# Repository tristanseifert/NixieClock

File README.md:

# Nixie Clock
A Nixie tube clock based on the Russian [IN-12A](http://www.tube-tester.com/sites/nixie/data/in-12a.htm) tubes. The clock is designed to be modular: one or more tube boards (which contain value latches, high voltage drivers, tube mounts, and current limiting resistors) can be connected to the control board (which contains a full 68008-based minicomputer!)

There is also provision for an USB FIFO (FT245R) for communication with a PC, a 32K NVRAM+RTC (DS1244) for timekeeping and configuration, a 100Hz periodic interrupt, and a connection to a Noritake CU24043-Y100 (or any other display with the same pinout) VFD.

The board is powered off of a regulated 12V supply, from which 5V and ~180V (for the anodes) is generated.

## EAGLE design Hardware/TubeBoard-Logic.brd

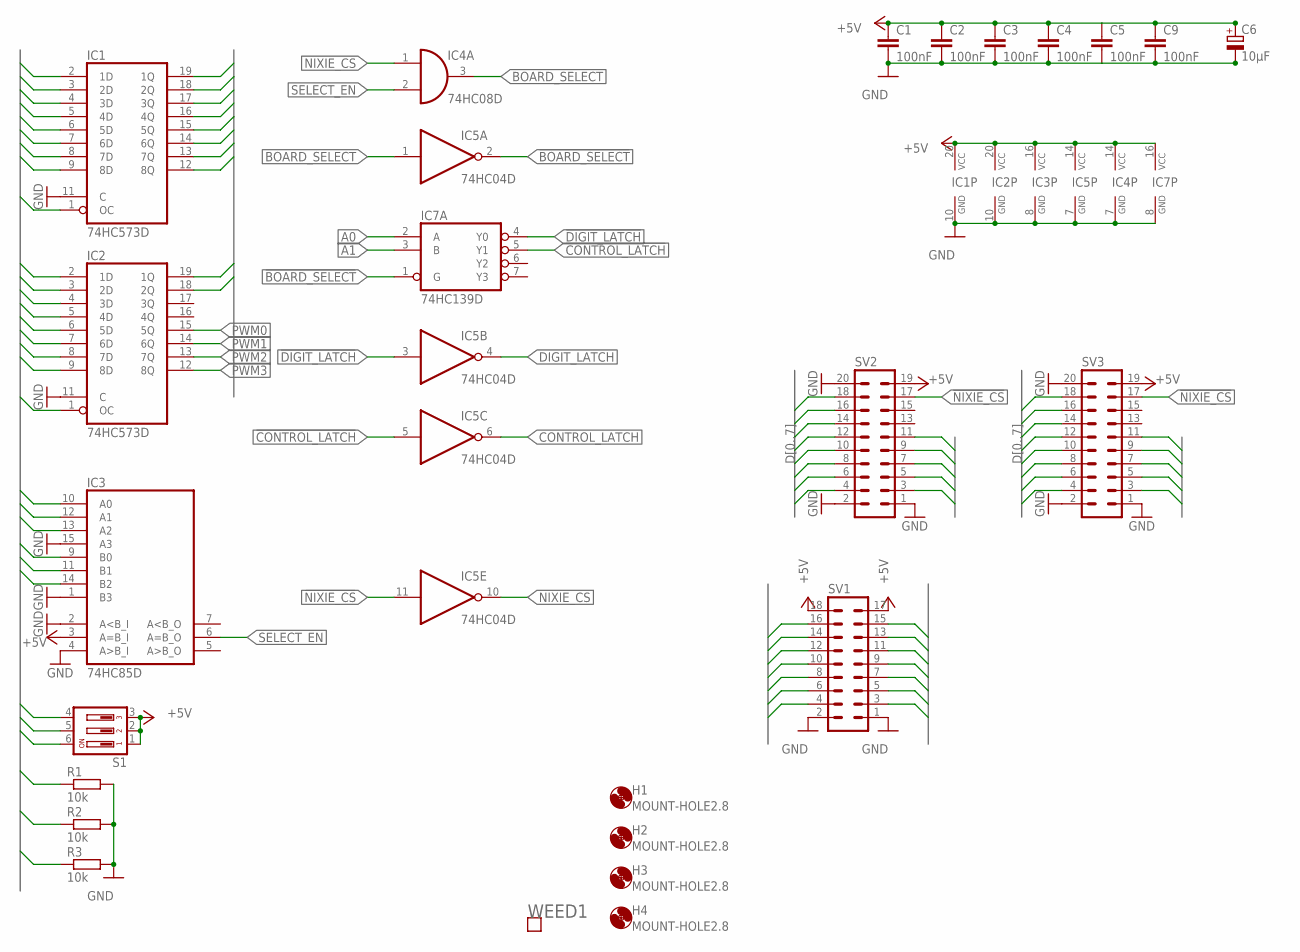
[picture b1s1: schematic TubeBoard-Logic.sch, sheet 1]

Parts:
C1, C2, C3, C4, C5, C9: 100nF; C1206
C6: 10µF; SMC_B; MOUSER 581-TAJB106K020RNJV
H1, H2, H3, H4: MOUNT-HOLE2.8; 2,8
IC1, IC2: 74HC573D; SO20W
IC3: 74HC85D; SO16; MOUSER 771-74HC85D-T
IC4: 74HC08D; SO14
IC5: 74HC04D; SO14
IC7: 74HC139D; SO16; MOUSER 771-HC139D652
R1, R2, R3: 10k; R2012; MOUSER 652-CR0805FX-1002ELF
S1: SD4-03; MOUSER 611-BDB03
SV1: MA09-2
SV2, SV3: MA10-2
WEED1: WEED; DOINK

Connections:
!BOARD_SELECT: IC5.2 (O), IC7.1 (G)
!CONTROL_LATCH: IC5.5 (I), IC7.5 (Y1)
!DIGIT_LATCH: IC5.3 (I), IC7.4 (Y0)
!NIXIE_CS: IC5.11 (I), SV2.17, SV3.17
+5V: C1.1, C2.1, C3.1, C4.1, C5.1, C6.+, C9.1, IC1.20 (VCC), IC2.20 (VCC), IC3.3 (A=B_I), IC3.16 (VCC), IC4.14 (VCC), IC5.14 (VCC), IC7.16 (VCC), S1.1, S1.2, S1.3, SV1.17, SV1.18, SV2.19, SV3.19
A0: IC7.2 (A), SV2.3, SV3.3
A1: IC7.3 (B), SV2.5, SV3.5
A2: IC3.10 (A0), SV2.7, SV3.7
A3: IC3.12 (A1), SV2.9, SV3.9
A4: IC3.13 (A2), SV2.11, SV3.11
BOARD_SELECT: IC4.3 (O), IC5.1 (I)
COLON_B: IC2.19 (1Q), SV1.8
COLON_T: IC2.18 (2Q), SV1.6
CONTROL_LATCH: IC2.1 (OC), IC5.6 (O)
D0: IC1.2 (1D), IC2.2 (1D), SV2.8, SV3.8
D1: IC1.3 (2D), IC2.3 (2D), SV2.6, SV3.6
D2: IC1.4 (3D), IC2.4 (3D), SV2.4, SV3.4
D3: IC1.5 (4D), IC2.5 (4D), SV2.10, SV3.10
D4: IC1.6 (5D), IC2.6 (5D), SV2.12, SV3.12
D5: IC1.7 (6D), IC2.7 (6D), SV2.14, SV3.14
D6: IC1.8 (7D), IC2.8 (7D), SV2.16, SV3.16
D7: IC1.9 (8D), IC2.9 (8D), SV2.18, SV3.18
DIGIT_LATCH: IC1.1 (OC), IC5.4 (O)
GND: C1.2, C2.2, C3.2, C4.2, C5.2, C6.-, C9.2, IC1.10 (GND), IC1.11 (C), IC2.10 (GND), IC2.11 (C), IC3.1 (B3), IC3.2 (A<B_I), IC3.4 (A>B_I), IC3.8 (GND), IC3.15 (A3), IC4.7 (GND), IC5.7 (GND), IC7.8 (GND), R1.2, R2.2, R3.2, SV1.1, SV1.2, SV2.1, SV2.2, SV2.20, SV3.1, SV3.2, SV3.20; also elsewhere on the board
ID0: IC3.9 (B0), R3.1, S1.6
ID1: IC3.11 (B1), R2.1, S1.5
ID2: IC3.14 (B2), R1.1, S1.4
LDIGIT0: IC1.19 (1Q), SV1.16
LDIGIT1: IC1.18 (2Q), SV1.14
LDIGIT2: IC1.17 (3Q), SV1.12
LDIGIT3: IC1.16 (4Q), SV1.10
NIXIE_CS: IC4.1 (I0), IC5.10 (O)
PWM0: IC2.15 (5Q), SV1.7
PWM1: IC2.14 (6Q), SV1.5
PWM2: IC2.13 (7Q), SV1.3
PWM3: IC2.12 (8Q), SV1.4
RDIGIT0: IC1.15 (5Q), SV1.15
RDIGIT1: IC1.14 (6Q), SV1.13
RDIGIT2: IC1.13 (7Q), SV1.11
RDIGIT3: IC1.12 (8Q), SV1.9
SELECT_EN: IC3.6 (A=B_O), IC4.2 (I1)

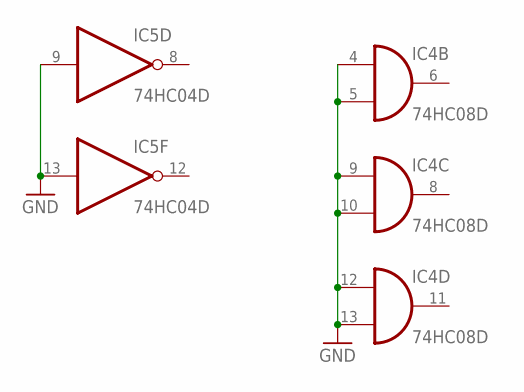
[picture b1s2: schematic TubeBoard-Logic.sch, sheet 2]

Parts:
IC4: 74HC08D; SO14
IC5: 74HC04D; SO14

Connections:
GND: IC4.4 (I0), IC4.5 (I1), IC4.9 (I0), IC4.10 (I1), IC4.12 (I0), IC4.13 (I1), IC5.9 (I), IC5.13 (I); also elsewhere on the board

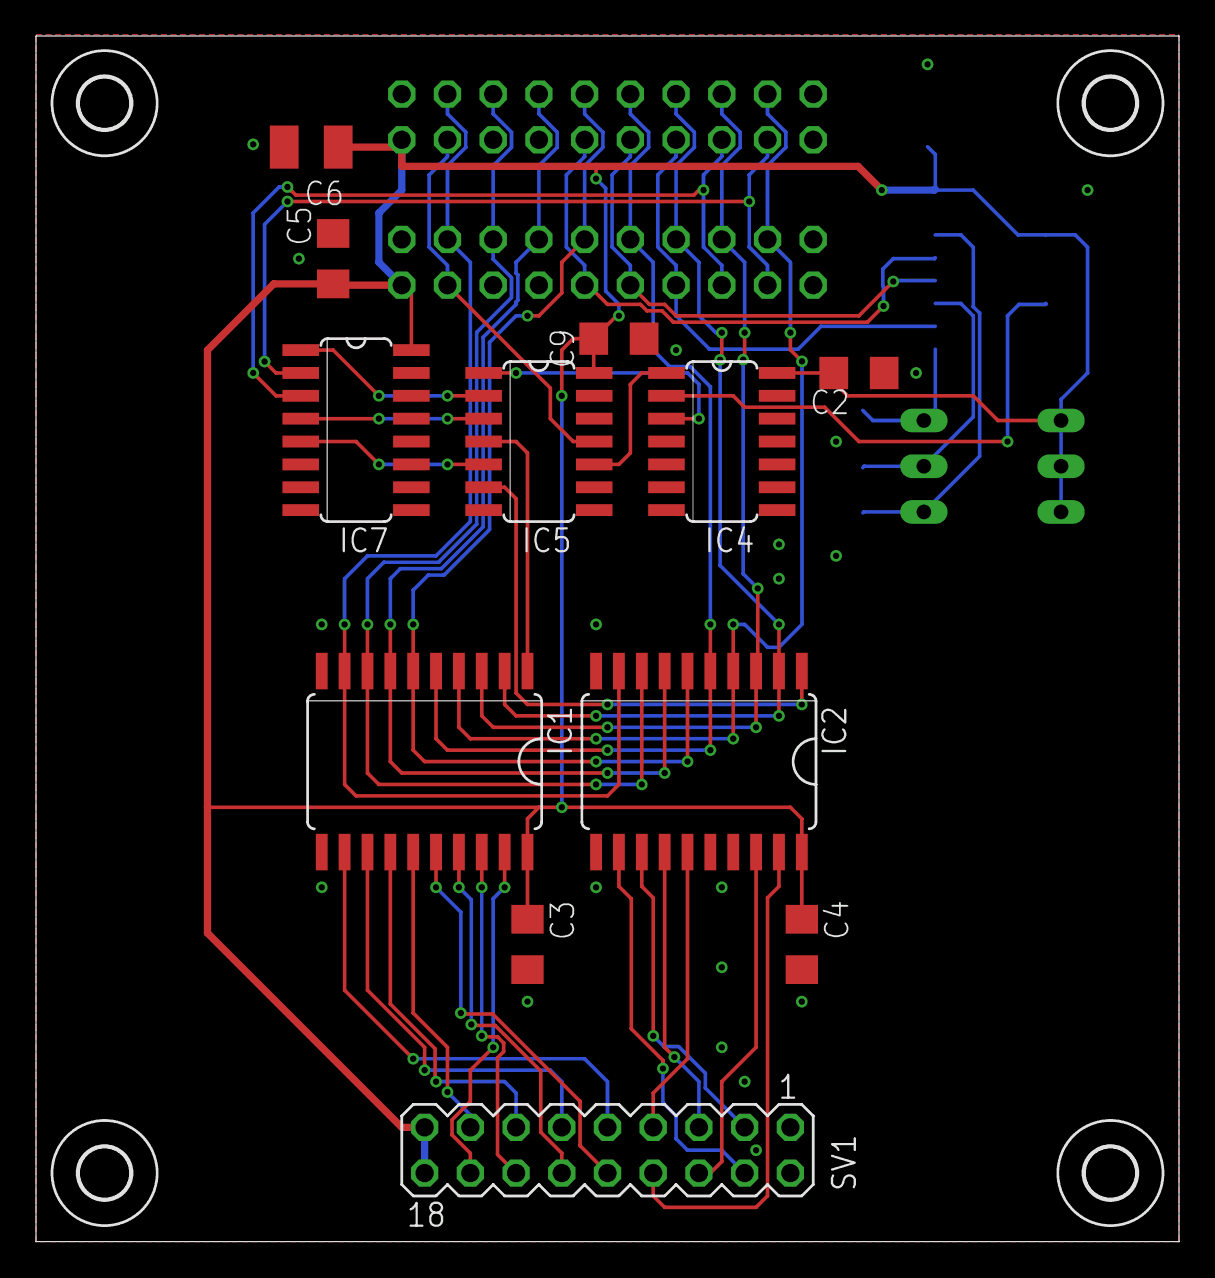
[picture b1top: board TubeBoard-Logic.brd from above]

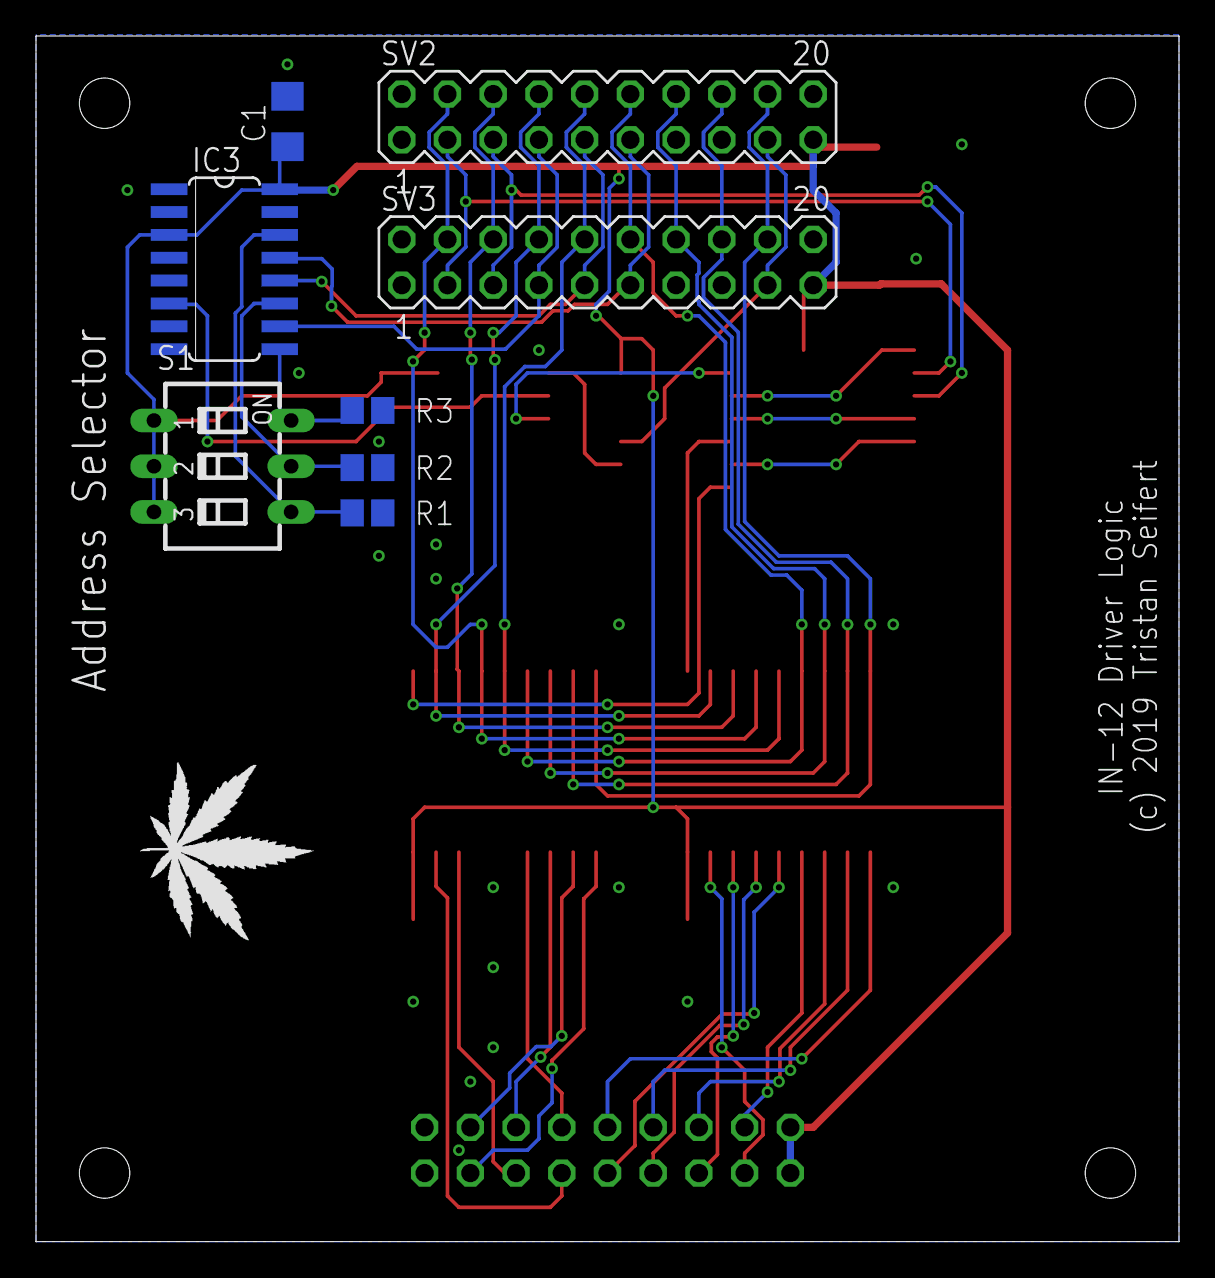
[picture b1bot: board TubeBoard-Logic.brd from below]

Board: 2 copper layers, 63.5 x 67.0 mm, 25 parts (9 on the bottom side), 41 nets.

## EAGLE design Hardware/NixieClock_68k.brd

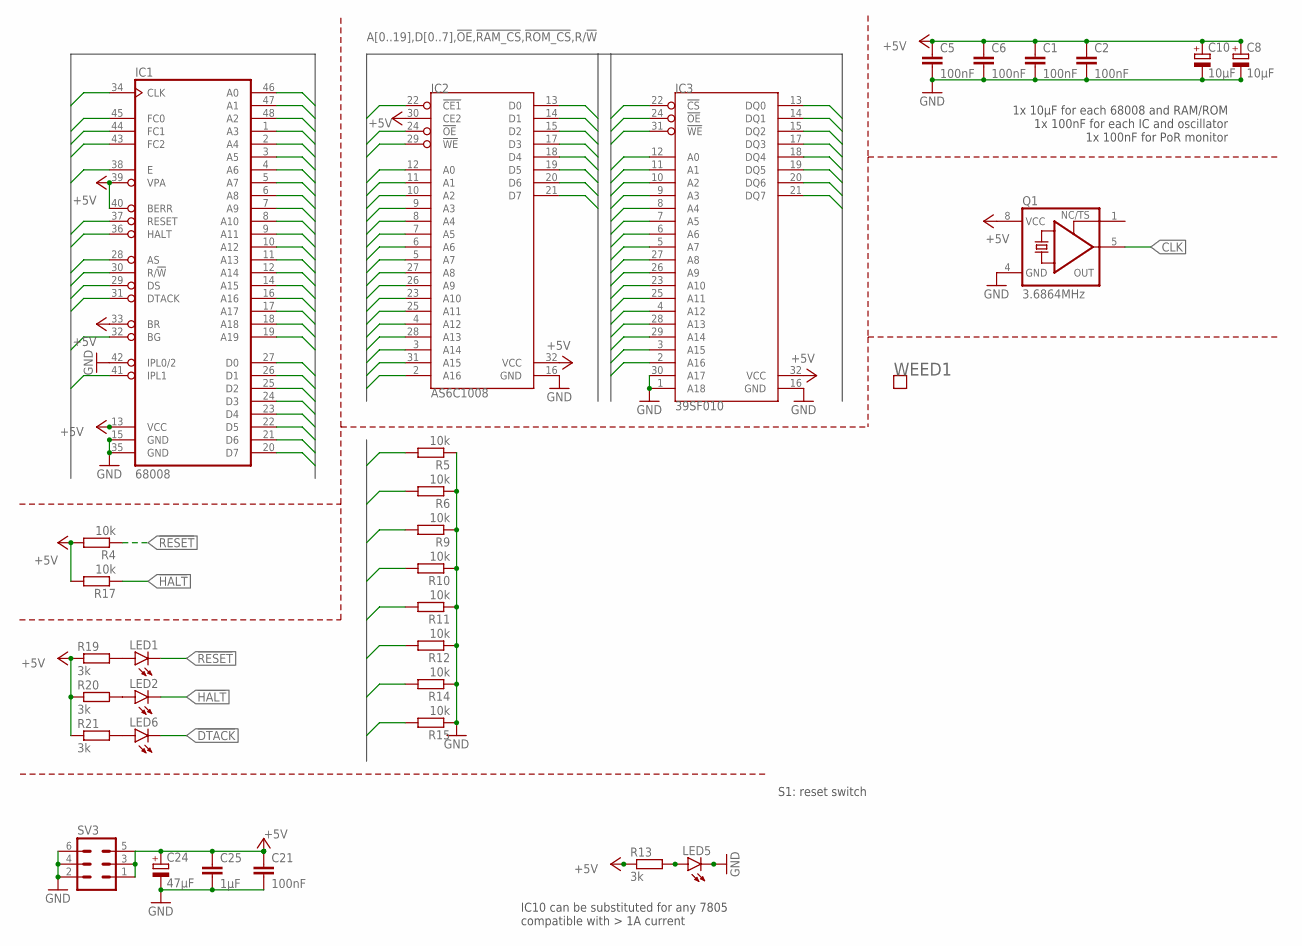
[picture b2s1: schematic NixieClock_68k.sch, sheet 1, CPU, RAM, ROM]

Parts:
C1, C2, C5, C6, C21: 100nF; C0805; MOUSER 710-885012207072
C8, C10: 10µF; SMC_B; MOUSER 581-TAJB106K020RNJV
C24: 47µF; CT6032; MOUSER 581-TAJD476M016RNJV
C25: 1µF; C0805; MOUSER 710-885012107015
IC1: 68008; DIL48
IC2: AS6C1008; DIL32
IC3: 39SF010; DIL32; MOUSER 804-39SF010A7CPHE
LED1, LED2: LEDCHIPLED_1206; CHIPLED_1206; MOUSER 710-156120RS75300
LED5: LEDCHIPLED_1206; CHIPLED_1206; MOUSER 710-156120YS75300
LED6: LEDCHIPLED_1206; CHIPLED_1206; MOUSER 710-156120VS75300
Q1: 3.6864MHz; DIL08S; MOUSER 774-MXO45HS-3C-3.6
R4, R5, R6, R9, R10, R11, R12, R14, R15, R17: 10k; R2012; MOUSER 652-CR0805FX-1002ELF
R13, R19, R20, R21: 3k; R2012; MOUSER 652-CR0805JW-302ELF
SV3: MA03-2
WEED1: WEED; DOINK

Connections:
!AS: IC1.28 (AS); also elsewhere on the board
!BG: IC1.32 (BG)
!DS: IC1.29 (DS)
!DTACK: IC1.31 (DTACK), LED6.C; also elsewhere on the board
!HALT: IC1.36 (HALT), LED2.C, R17.1; also elsewhere on the board
!IPL1: IC1.41 (IPL1); also elsewhere on the board
!OE: IC2.24 (!OE), IC3.24 (!OE); also elsewhere on the board
!RAM_CS: IC2.22 (!CE1); also elsewhere on the board
!RESET: IC1.37 (RESET), LED1.C, R4.1; also elsewhere on the board
!ROM_CS: IC3.22 (!CS); also elsewhere on the board
+5V: C1.1, C2.1, C5.1, C6.1, C8.+, C10.+, C21.1, C24.+, C25.1, IC1.13 (VCC), IC1.33 (BR), IC1.39 (VPA), IC1.40 (BERR), IC2.30 (CE2), IC2.32 (VCC), IC3.32 (VCC), Q1.8 (VCC), R4.2, R13.1, R17.2, R19.1, R20.1, R21.1, SV3.1, SV3.3, SV3.5; also elsewhere on the board
A0: IC1.46 (A0), IC2.12 (A0), IC3.12 (A0); also elsewhere on the board
A1: IC1.47 (A1), IC2.11 (A1), IC3.11 (A1); also elsewhere on the board
A2: IC1.48 (A2), IC2.10 (A2), IC3.10 (A2); also elsewhere on the board
A3: IC1.1 (A3), IC2.9 (A3), IC3.9 (A3); also elsewhere on the board
A4: IC1.2 (A4), IC2.8 (A4), IC3.8 (A4); also elsewhere on the board
A5: IC1.3 (A5), IC2.7 (A5), IC3.7 (A5); also elsewhere on the board
A6: IC1.4 (A6), IC2.6 (A6), IC3.6 (A6); also elsewhere on the board
A7: IC1.5 (A7), IC2.5 (A7), IC3.5 (A7); also elsewhere on the board
A8: IC1.6 (A8), IC2.27 (A8), IC3.27 (A8); also elsewhere on the board
A9: IC1.7 (A9), IC2.26 (A9), IC3.26 (A9); also elsewhere on the board
A10: IC1.8 (A10), IC2.23 (A10), IC3.23 (A10); also elsewhere on the board
A11: IC1.9 (A11), IC2.25 (A11), IC3.25 (A11); also elsewhere on the board
A12: IC1.10 (A12), IC2.4 (A12), IC3.4 (A12); also elsewhere on the board
A13: IC1.11 (A13), IC2.28 (A13), IC3.28 (A13); also elsewhere on the board
A14: IC1.12 (A14), IC2.3 (A14), IC3.29 (A14); also elsewhere on the board
A15: IC1.14 (A15), IC2.31 (A15), IC3.3 (A15)
A16: IC1.16 (A16), IC2.2 (A16), IC3.2 (A16); also elsewhere on the board
A17: IC1.17 (A17); also elsewhere on the board
A18: IC1.18 (A18); also elsewhere on the board
A19: IC1.19 (A19)
CLK: IC1.34 (CLK), Q1.5 (OUT); also elsewhere on the board
D0: IC1.27 (D0), IC2.13 (D0), IC3.13 (DQ0), R5.2; also elsewhere on the board
D1: IC1.26 (D1), IC2.14 (D1), IC3.14 (DQ1), R6.2; also elsewhere on the board
D2: IC1.25 (D2), IC2.15 (D2), IC3.15 (DQ2), R9.2; also elsewhere on the board
D3: IC1.24 (D3), IC2.17 (D3), IC3.17 (DQ3), R10.2; also elsewhere on the board
D4: IC1.23 (D4), IC2.18 (D4), IC3.18 (DQ4), R11.2; also elsewhere on the board
D5: IC1.22 (D5), IC2.19 (D5), IC3.19 (DQ5), R12.2; also elsewhere on the board
D6: IC1.21 (D6), IC2.20 (D6), IC3.20 (DQ6), R14.2; also elsewhere on the board
D7: IC1.20 (D7), IC2.21 (D7), IC3.21 (DQ7), R15.2; also elsewhere on the board
E: IC1.38 (E)
FC0: IC1.45 (FC0); also elsewhere on the board
FC1: IC1.44 (FC1); also elsewhere on the board
FC2: IC1.43 (FC2); also elsewhere on the board
GND: C1.2, C2.2, C5.2, C6.2, C8.-, C10.-, C21.2, C24.-, C25.2, IC1.15 (GND), IC1.35 (GND), IC1.42 (IPL0/2), IC2.16 (GND), IC3.1 (A18), IC3.16 (GND), IC3.30 (A17), LED5.C, Q1.4 (GND), R5.1, R6.1, R9.1, R10.1, R11.1, R12.1, R14.1, R15.1, SV3.2, SV3.4, SV3.6; also elsewhere on the board
unnamed: LED1.A, R19.2
unnamed: LED5.A, R13.2
unnamed: LED2.A, R20.2
unnamed: LED6.A, R21.2
R/!W!: IC1.30 (R/!W), IC2.29 (!WE), IC3.31 (!WE); also elsewhere on the board

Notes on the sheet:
1x 10µF for each 68008 and RAM/ROM 1x 100nF for each IC and oscillator 1x 100nF for PoR monitor
IC10 can be substituted for any 7805 compatible with > 1A current
S1: reset switch

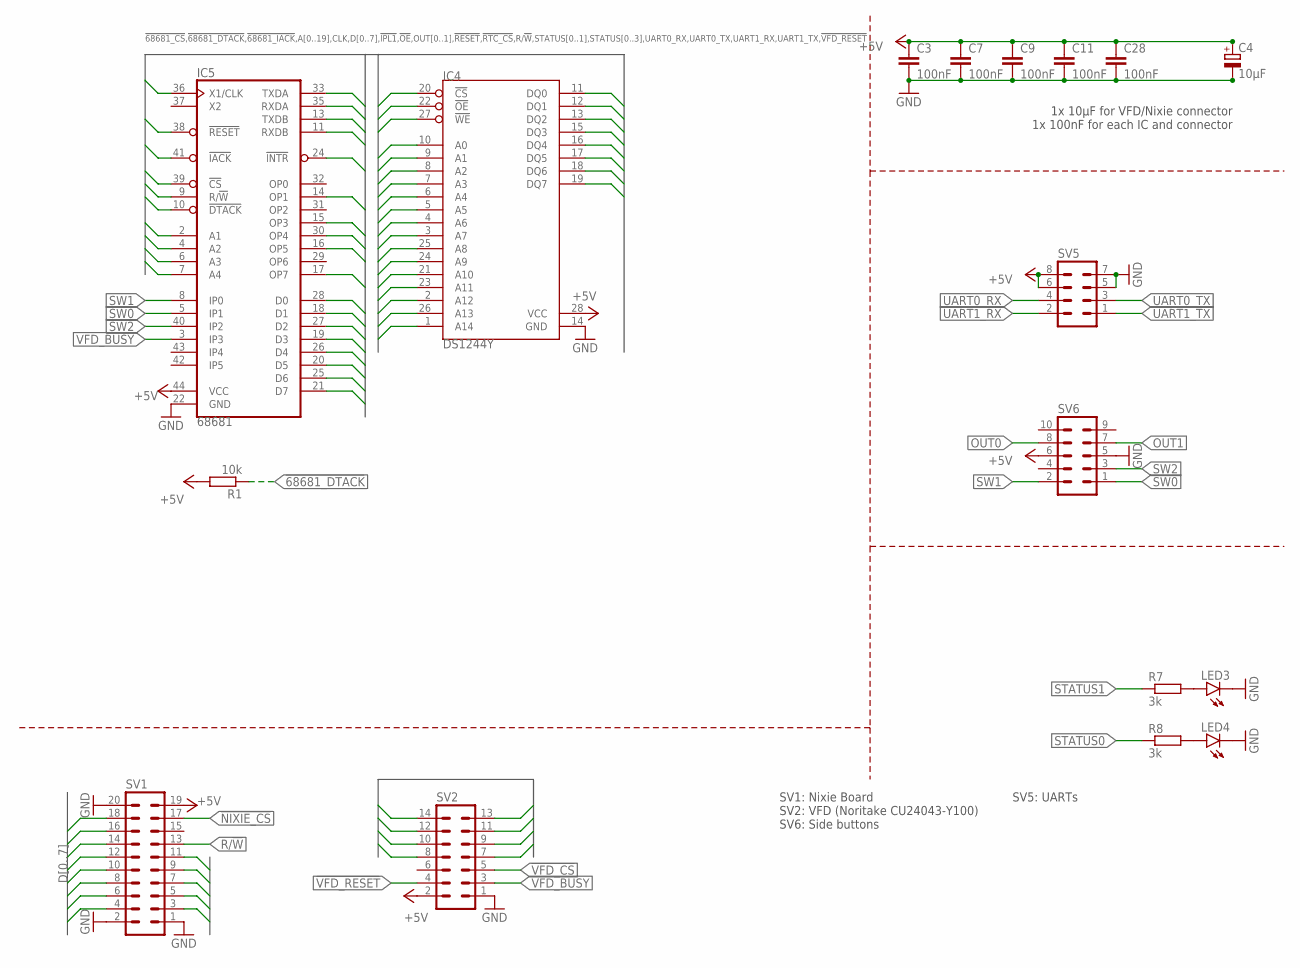
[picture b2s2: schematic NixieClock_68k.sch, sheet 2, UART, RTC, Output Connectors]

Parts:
C3, C7, C9, C11, C28: 100nF; C0805; MOUSER 710-885012207072
C4: 10µF; SMC_B; MOUSER 581-TAJB106K020RNJV
IC4: DS1244Y; DIL28-6
IC5: 68681; PLCC-S44
LED3, LED4: LEDCHIPLED_1206; CHIPLED_1206; MOUSER 710-156120VS75300
R1: 10k; R2012; MOUSER 652-CR0805FX-1002ELF
R7, R8: 3k; R2012; MOUSER 652-CR0805JW-302ELF
SV1: MA10-2
SV2: MA07-2
SV5: MA04-2
SV6: MA05-2

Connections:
!68681_CS: IC5.39 (!CS); also elsewhere on the board
!68681_DTACK: IC5.10 (!DTACK), R1.1; also elsewhere on the board
!68681_IACK: IC5.41 (!IACK); also elsewhere on the board
!IPL1: IC5.24 (!INTR); also elsewhere on the board
!NIXIE_CS: SV1.17; also elsewhere on the board
!OE: IC4.22 (!OE); also elsewhere on the board
!RESET: IC5.38 (!RESET); also elsewhere on the board
!RTC_CS: IC4.20 (!CS); also elsewhere on the board
!VFD_CS: SV2.5; also elsewhere on the board
!VFD_RESET: IC5.30 (OP4), SV2.4
+5V: C3.1, C4.+, C7.1, C9.1, C11.1, C28.1, IC4.28 (VCC), IC5.44 (VCC), R1.2, SV1.19, SV2.2, SV5.6, SV5.8, SV6.6; also elsewhere on the board
A0: IC4.10 (A0), IC5.2 (A1), SV1.3; also elsewhere on the board
A1: IC4.9 (A1), IC5.4 (A2), SV1.5; also elsewhere on the board
A2: IC4.8 (A2), IC5.6 (A3), SV1.7; also elsewhere on the board
A3: IC4.7 (A3), IC5.7 (A4), SV1.9; also elsewhere on the board
A4: IC4.6 (A4), SV1.11; also elsewhere on the board
A5: IC4.5 (A5); also elsewhere on the board
A6: IC4.4 (A6); also elsewhere on the board
A7: IC4.3 (A7); also elsewhere on the board
A8: IC4.25 (A8); also elsewhere on the board
A9: IC4.24 (A9); also elsewhere on the board
A10: IC4.21 (A10); also elsewhere on the board
A11: IC4.23 (A11); also elsewhere on the board
A12: IC4.2 (A12); also elsewhere on the board
A13: IC4.26 (A13); also elsewhere on the board
A14: IC4.1 (A14); also elsewhere on the board
CLK: IC5.36 (X1/CLK); also elsewhere on the board
D0: IC4.11 (DQ0), IC5.28 (D0), SV1.8, SV2.7; also elsewhere on the board
D1: IC4.12 (DQ1), IC5.18 (D1), SV1.6, SV2.8; also elsewhere on the board
D2: IC4.13 (DQ2), IC5.27 (D2), SV1.4, SV2.9; also elsewhere on the board
D3: IC4.15 (DQ3), IC5.19 (D3), SV1.10, SV2.10; also elsewhere on the board
D4: IC4.16 (DQ4), IC5.26 (D4), SV1.12, SV2.11; also elsewhere on the board
D5: IC4.17 (DQ5), IC5.20 (D5), SV1.14, SV2.12; also elsewhere on the board
D6: IC4.18 (DQ6), IC5.25 (D6), SV1.16, SV2.13; also elsewhere on the board
D7: IC4.19 (DQ7), IC5.21 (D7), SV1.18, SV2.14; also elsewhere on the board
GND: C3.2, C4.-, C7.2, C9.2, C11.2, C28.2, IC4.14 (GND), IC5.22 (GND), LED3.C, LED4.C, SV1.1, SV1.2, SV1.20, SV2.1, SV5.5, SV5.7, SV6.5; also elsewhere on the board
unnamed: LED3.A, R7.2
unnamed: LED4.A, R8.2
OUT0: IC5.15 (OP3), SV6.8
OUT1: IC5.14 (OP1), SV6.7
R/!W!: IC4.27 (!WE), IC5.9 (R/!W), SV1.13; also elsewhere on the board
STATUS0: IC5.17 (OP7), R8.1
STATUS1: IC5.16 (OP5), R7.1
SW0: IC5.5 (IP1), SV6.1
SW1: IC5.8 (IP0), SV6.2
SW2: IC5.40 (IP2), SV6.3
UART0_RX: IC5.35 (RXDA), SV5.4
UART0_TX: IC5.33 (TXDA), SV5.3
UART1_RX: IC5.11 (RXDB), SV5.2
UART1_TX: IC5.13 (TXDB), SV5.1
VFD_BUSY: IC5.3 (IP3), SV2.3

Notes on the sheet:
SV1: Nixie Board SV2: VFD (Noritake CU24043-Y100) SV6: Side buttons
1x 10µF for VFD/Nixie connector 1x 100nF for each IC and connector
SV5: UARTs

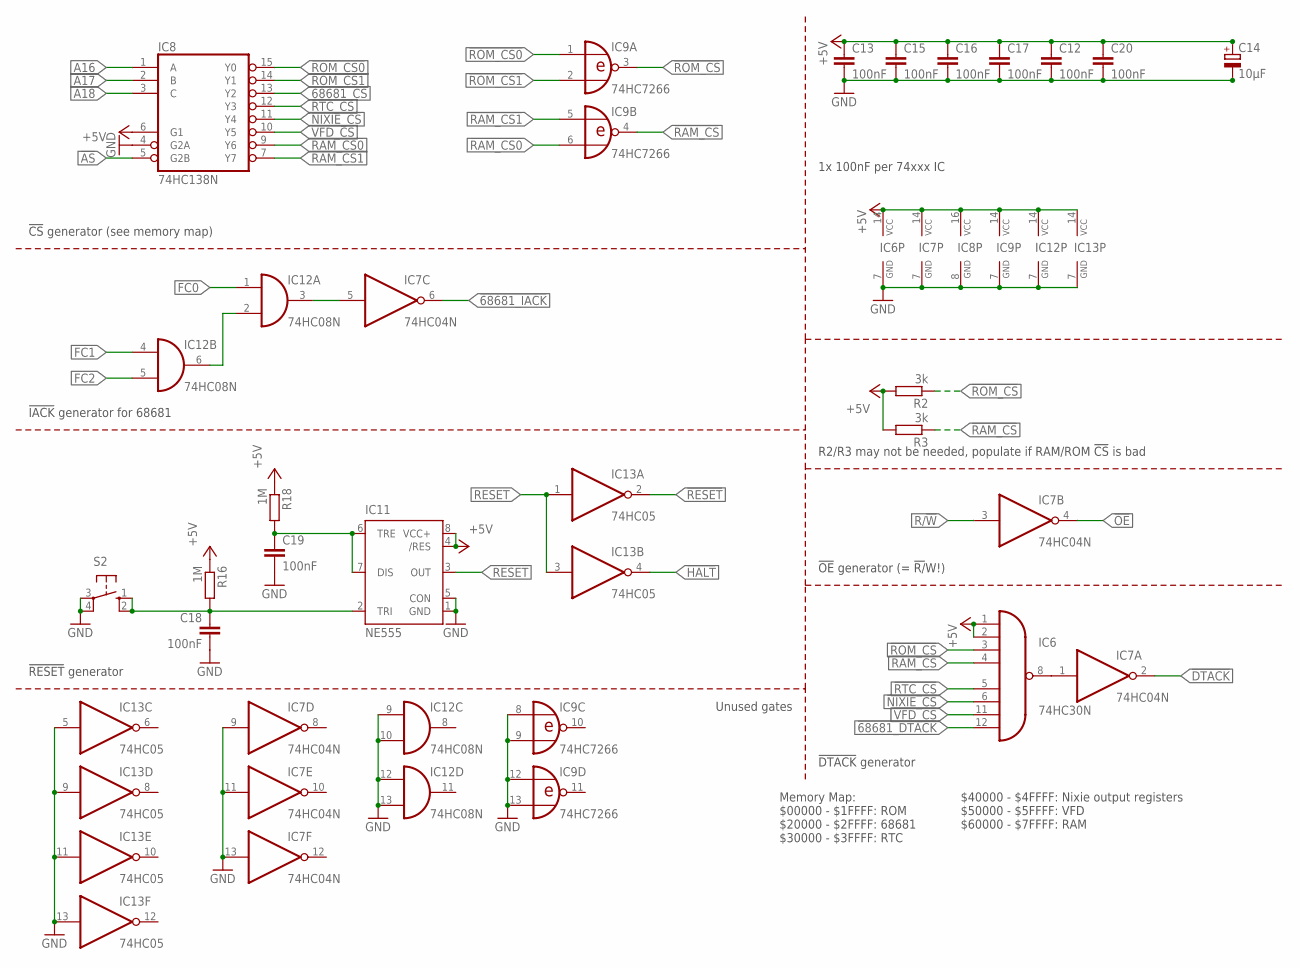
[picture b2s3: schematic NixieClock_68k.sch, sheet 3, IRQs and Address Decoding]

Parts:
C12, C13, C15, C16, C17, C18, C20: 100nF; C0805; MOUSER 710-885012207072
C14: 10µF; SMC_B; MOUSER 581-TAJB106K020RNJV
C19: 100nF; C0805; MOUSER 710-885012207078
IC6: 74HC30N; DIL14; MOUSER 595-CD74HC30E
IC7: 74HC04N; DIL14; MOUSER 595-SN74HC04AN
IC8: 74HC138N; DIL16; MOUSER 595-SN74HC138N
IC9: 74HC7266; DIL14; MOUSER 595-CD74HC7266E
IC11: NE555; DIL-08; MOUSER 595-NE555P
IC12: 74HC08N; DIL14; MOUSER 595-SN74HC08AN
IC13: 74HC05; DIL14; MOUSER 595-SN74HC05N
R2, R3: 3k; R2012; MOUSER 652-CR0805JW-302ELF
R16, R18: 1M; R2012; MOUSER 652-CR0805FX-18R2ELF
S2: 10-XX; B3F-10XX; MOUSER 653-B3F-1052

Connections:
!68681_CS: IC8.13 (Y2); also elsewhere on the board
!68681_DTACK: IC6.12 (I7); also elsewhere on the board
!68681_IACK: IC7.6 (O); also elsewhere on the board
!AS: IC8.5 (G2B); also elsewhere on the board
!DTACK: IC7.2 (O); also elsewhere on the board
!HALT: IC13.4 (O); also elsewhere on the board
!NIXIE_CS: IC6.6 (I5), IC8.11 (Y4); also elsewhere on the board
!OE: IC7.4 (O); also elsewhere on the board
!RAM_CS: IC6.4 (I3), IC9.4 (O), R3.1; also elsewhere on the board
!RAM_CS0: IC8.9 (Y6), IC9.6 (I1)
!RAM_CS1: IC8.7 (Y7), IC9.5 (I0)
!RESET: IC13.2 (O); also elsewhere on the board
!ROM_CS: IC6.3 (I2), IC9.3 (O), R2.1; also elsewhere on the board
!ROM_CS0: IC8.15 (Y0), IC9.1 (I0)
!ROM_CS1: IC8.14 (Y1), IC9.2 (I1)
!RTC_CS: IC6.5 (I4), IC8.12 (Y3); also elsewhere on the board
!VFD_CS: IC6.11 (I6), IC8.10 (Y5); also elsewhere on the board
+5V: C12.1, C13.1, C14.+, C15.1, C16.1, C17.1, C20.1, IC6.1 (I0), IC6.2 (I1), IC6.14 (VCC), IC7.14 (VCC), IC8.6 (G1), IC8.16 (VCC), IC9.14 (VCC), IC11.4 (/RES), IC11.8 (VCC+), IC12.14 (VCC), IC13.14 (VCC), R2.2, R3.2, R16.1, R18.1; also elsewhere on the board
A16: IC8.1 (A); also elsewhere on the board
A17: IC8.2 (B); also elsewhere on the board
A18: IC8.3 (C); also elsewhere on the board
FC0: IC12.1 (I0); also elsewhere on the board
FC1: IC12.4 (I0); also elsewhere on the board
FC2: IC12.5 (I1); also elsewhere on the board
GND: C12.2, C13.2, C14.-, C15.2, C16.2, C17.2, C18.2, C19.2, C20.2, IC6.7 (GND), IC7.7 (GND), IC7.9 (I), IC7.11 (I), IC7.13 (I), IC8.4 (G2A), IC8.8 (GND), IC9.7 (GND), IC9.8 (I0), IC9.9 (I1), IC9.12 (I0), IC9.13 (I1), IC11.1 (GND), IC11.5 (CON), IC12.7 (GND), IC12.9 (I0), IC12.10 (I1), IC12.12 (I0), IC12.13 (I1), IC13.5 (I), IC13.7 (GND), IC13.9 (I), IC13.11 (I), IC13.13 (I), S2.3, S2.4 (P1); also elsewhere on the board
unnamed: C18.1, IC11.2 (TRI), R16.2, S2.1 (S), S2.2 (S1)
unnamed: IC6.8 (O), IC7.1 (I)
unnamed: IC7.5 (I), IC12.3 (O)
unnamed: IC12.2 (I1), IC12.6 (O)
unnamed: C19.1, IC11.6 (TRE), IC11.7 (DIS), R18.2
R/!W!: IC7.3 (I); also elsewhere on the board
RESET: IC11.3 (OUT), IC13.1 (I), IC13.3 (I)

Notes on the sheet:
Memory Map: $00000 - $1FFFF: ROM $20000 - $2FFFF: 68681 $30000 - $3FFFF: RTC
1x 100nF per 74xxx IC
!DTACK! generator
!OE! generator (= !R/!W!)
!CS! generator (see memory map)
!IACK! generator for 68681
$40000 - $4FFFF: Nixie output registers $50000 - $5FFFF: VFD $60000 - $7FFFF: RAM
!RESET! generator
Unused gates
R2/R3 may not be needed, populate if RAM/ROM !CS! is bad

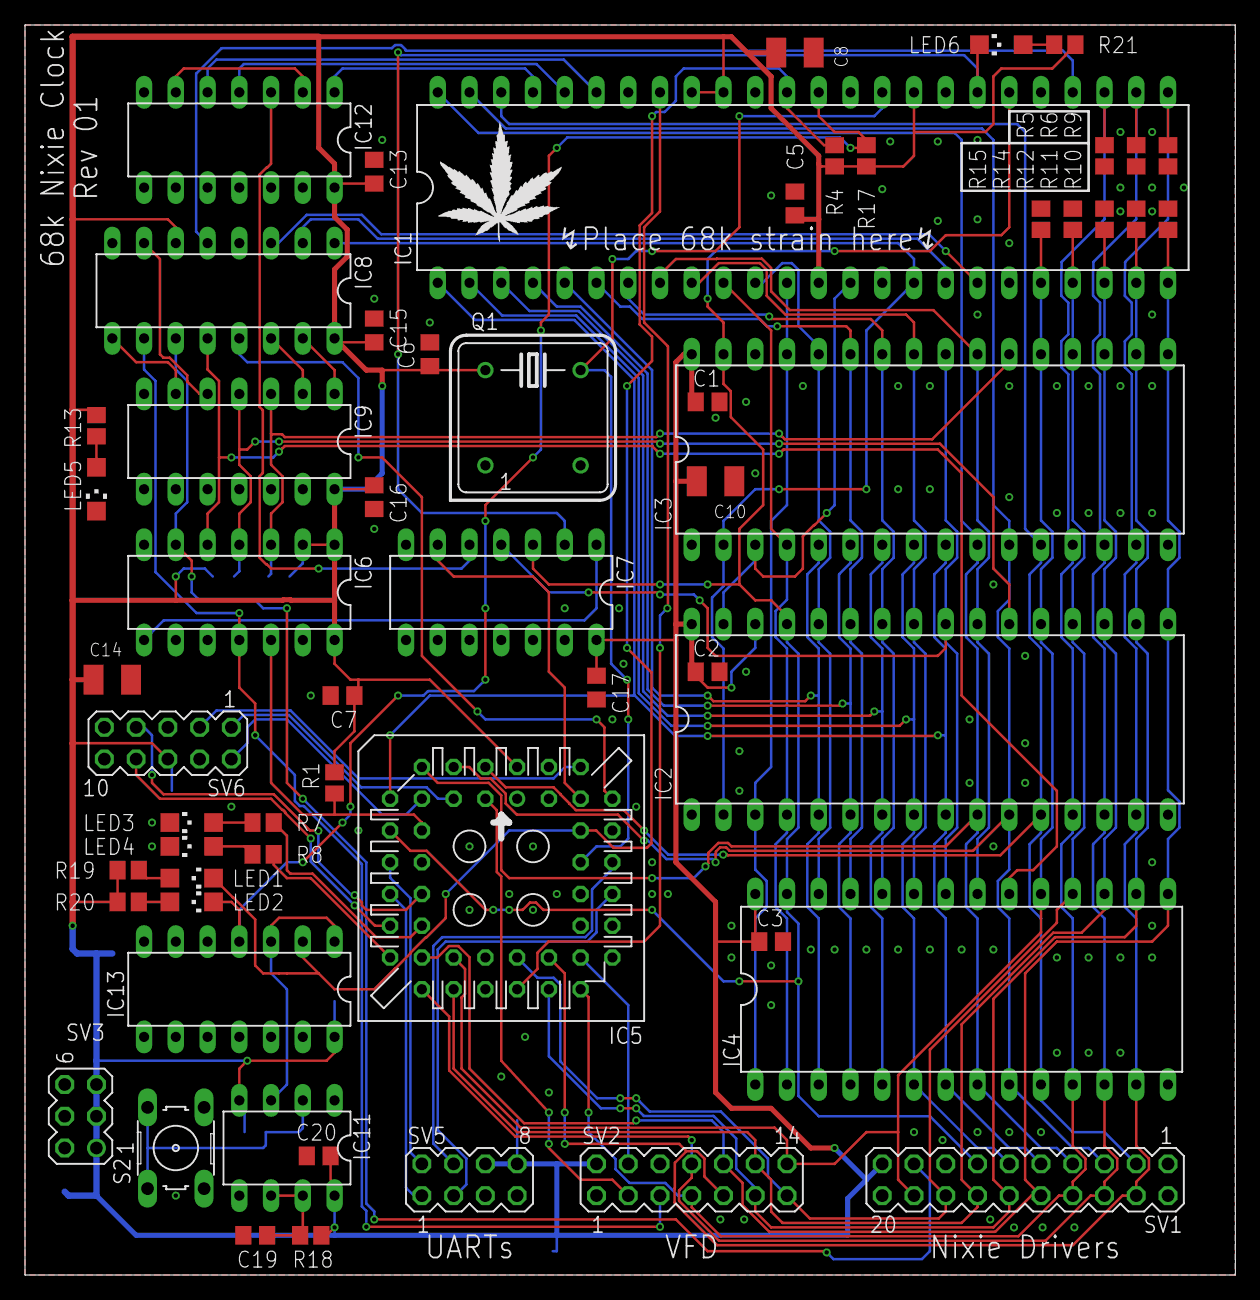
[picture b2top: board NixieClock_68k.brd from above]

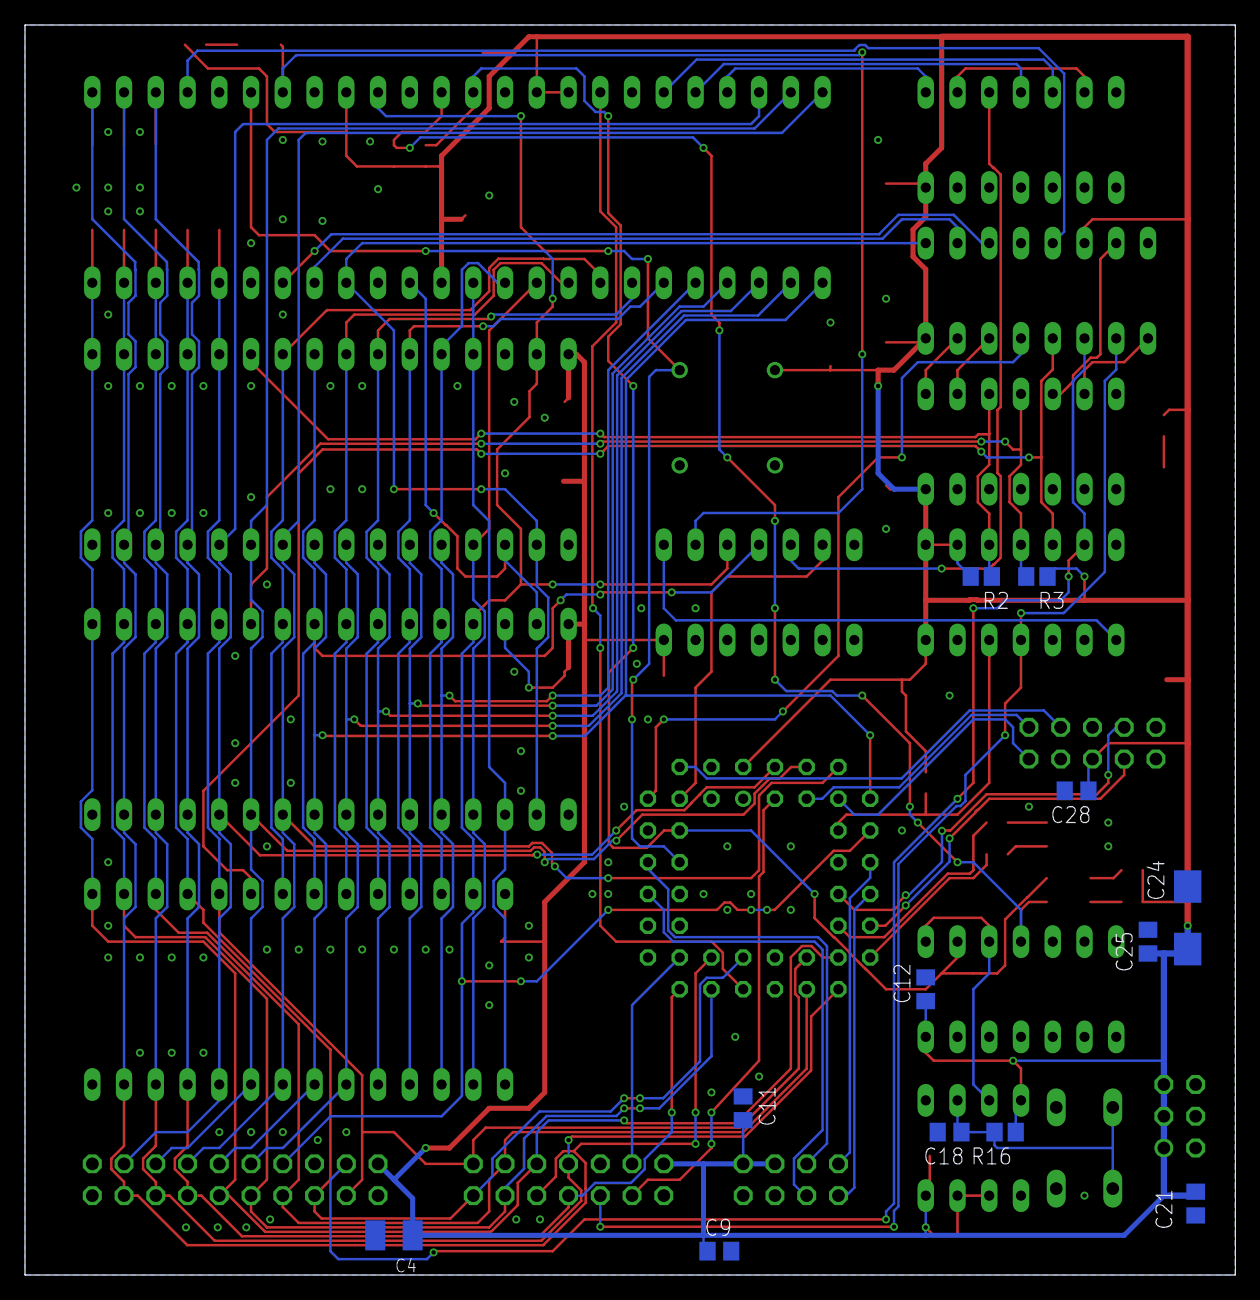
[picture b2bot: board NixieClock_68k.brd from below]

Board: 2 copper layers, 96.8 x 100.0 mm, 71 parts (12 on the bottom side), 77 nets.

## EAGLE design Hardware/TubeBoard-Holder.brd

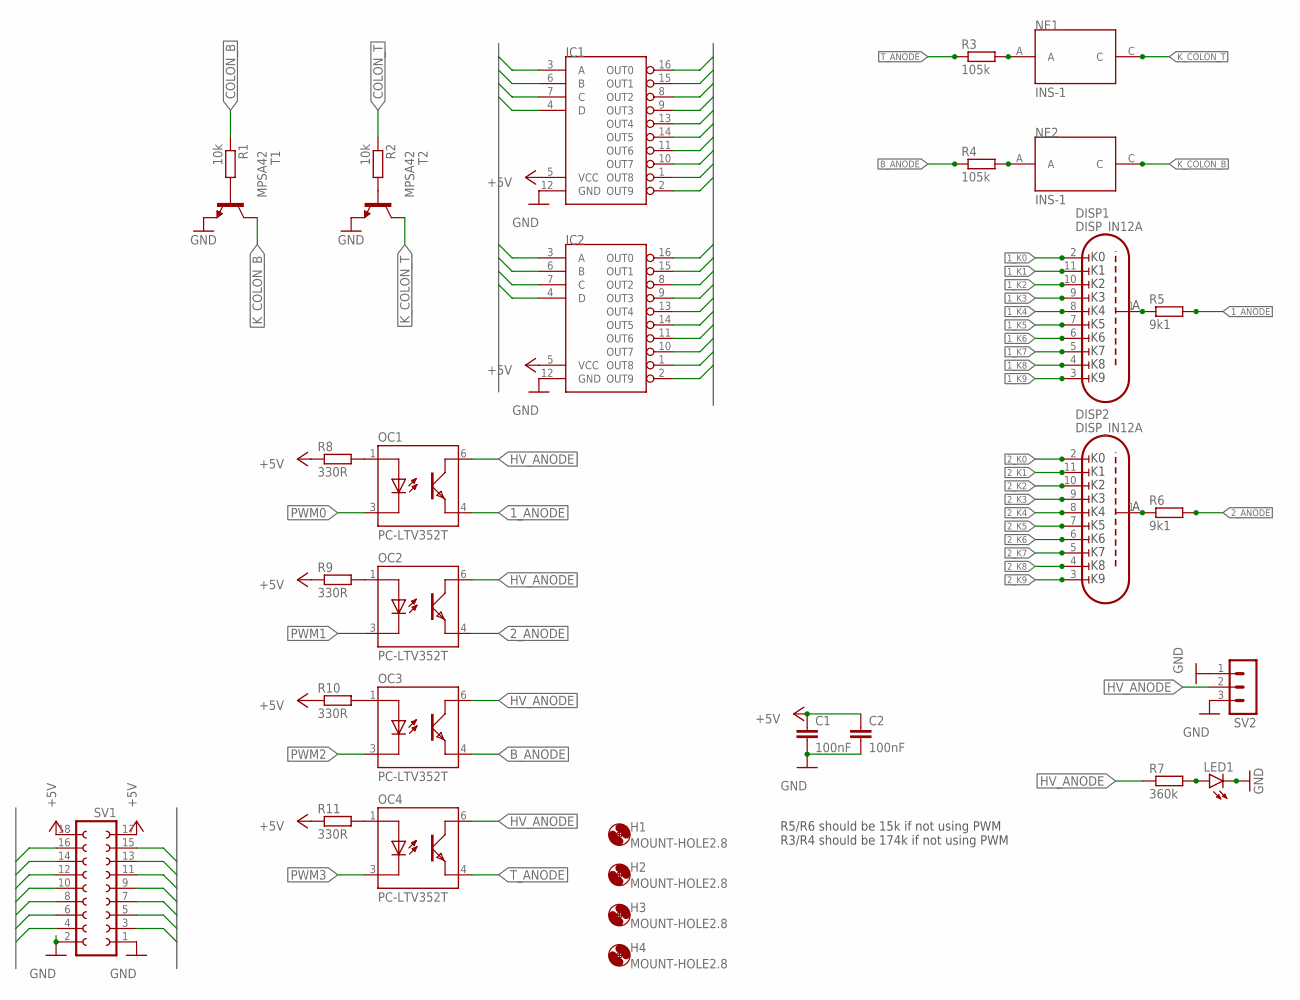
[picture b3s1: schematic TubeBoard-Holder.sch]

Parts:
C1, C2: 100nF; C1206
DISP1, DISP2: DISP_IN12A; DISP_IN-12_SOCKET
H1, H2, H3, H4: MOUNT-HOLE2.8; 2,8
IC1, IC2: 7441DIL16; DIL16
LED1: LEDCHIPLED_1206; CHIPLED_1206; MOUSER 710-156120RS75300
NE1, NE2: INS-1
OC1, OC2, OC3, OC4: PC-LTV352T; MINIFLAT4; MOUSER 859-LTV-352T
R1, R2: 10k; R2012; MOUSER 652-CR0805FX-1002ELF
R3, R4: 105k; M1206; MOUSER 667-ERJ-8ENF1053V
R5, R6: 9k1; 0411/12
R7: 360k; R2012; MOUSER 652-CR0805-JW-364ELF
R8, R9, R10, R11: 330R; R2012; MOUSER 652-CR0805FX-3300ELF
SV1: FE09-2
SV2: MA03-1
T1, T2: MPSA42; TO92-EBC; MOUSER 833-MPSA42-AP

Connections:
1_ANODE: OC1.4 (TE), R5.2
1_K0: DISP1.2 (K0), IC1.16 (OUT0)
1_K1: DISP1.11 (K1), IC1.15 (OUT1)
1_K2: DISP1.10 (K2), IC1.8 (OUT2)
1_K3: DISP1.9 (K3), IC1.9 (OUT3)
1_K4: DISP1.8 (K4), IC1.13 (OUT4)
1_K5: DISP1.7 (K5), IC1.14 (OUT5)
1_K6: DISP1.6 (K6), IC1.11 (OUT6)
1_K7: DISP1.5 (K7), IC1.10 (OUT7)
1_K8: DISP1.4 (K8), IC1.1 (OUT8)
1_K9: DISP1.3 (K9), IC1.2 (OUT9)
2_ANODE: OC2.4 (TE), R6.2
2_K0: DISP2.2 (K0), IC2.16 (OUT0)
2_K1: DISP2.11 (K1), IC2.15 (OUT1)
2_K2: DISP2.10 (K2), IC2.8 (OUT2)
2_K3: DISP2.9 (K3), IC2.9 (OUT3)
2_K4: DISP2.8 (K4), IC2.13 (OUT4)
2_K5: DISP2.7 (K5), IC2.14 (OUT5)
2_K6: DISP2.6 (K6), IC2.11 (OUT6)
2_K7: DISP2.5 (K7), IC2.10 (OUT7)
2_K8: DISP2.4 (K8), IC2.1 (OUT8)
2_K9: DISP2.3 (K9), IC2.2 (OUT9)
+5V: C1.1, C2.1, IC1.5 (VCC), IC2.5 (VCC), R8.1, R9.1, R10.1, R11.1, SV1.17, SV1.18
B_ANODE: OC3.4 (TE), R4.1
COLON_B: R1.1, SV1.8
COLON_T: R2.1, SV1.6
GND: C1.2, C2.2, IC1.12 (GND), IC2.12 (GND), LED1.C, SV1.1, SV1.2, SV2.1, SV2.3, T1.E, T2.E
HV_ANODE: OC1.6 (TC), OC2.6 (TC), OC3.6 (TC), OC4.6 (TC), R7.1, SV2.2
K_COLON_B: NE2.C, T1.C
K_COLON_T: NE1.C, T2.C
LDIGIT0: IC1.3 (A), SV1.16
LDIGIT1: IC1.6 (B), SV1.14
LDIGIT2: IC1.7 (C), SV1.12
LDIGIT3: IC1.4 (D), SV1.10
unnamed: DISP1.1 (ANODE), R5.1
unnamed: DISP2.1 (ANODE), R6.1
unnamed: NE1.A, R3.2
unnamed: NE2.A, R4.2
unnamed: R1.2, T1.B
unnamed: R2.2, T2.B
unnamed: OC1.1 (A), R8.2
unnamed: LED1.A, R7.2
unnamed: OC2.1 (A), R9.2
unnamed: OC3.1 (A), R10.2
unnamed: OC4.1 (A), R11.2
PWM0: OC1.3 (C), SV1.7
PWM1: OC2.3 (C), SV1.5
PWM2: OC3.3 (C), SV1.3
PWM3: OC4.3 (C), SV1.4
RDIGIT0: IC2.3 (A), SV1.15
RDIGIT1: IC2.6 (B), SV1.13
RDIGIT2: IC2.7 (C), SV1.11
RDIGIT3: IC2.4 (D), SV1.9
T_ANODE: OC4.4 (TE), R3.1

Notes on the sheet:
R5/R6 should be 15k if not using PWM R3/R4 should be 174k if not using PWM

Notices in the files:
Hardware/TubeBoard-Logic.brd:
(c) 2019 Tristan Seifert
TubeBoard.brd:
(c) 2018 Tristan Seifert
